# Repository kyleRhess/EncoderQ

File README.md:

# EncoderQ

## A realtime embedded C program for interfacing with incremental rotary encoders

 This code has been written for and tested on an ARM STM32F4 processor with a timer peripheral that supports for quadrature encoder input.
\
\
Currently, the processor hardware from the [DroneFluxx](https://github.com/kyleRhess/DroneFluxx) project is being used for testing firmware.
\
The only rotary encoder that has been tested so far is the [E6D-C](http://www.ia.omron.com/data_pdf/cat/e6d-c_ds_e_5_1_csm497.pdf) from Omron. This is a 6,000 pulse/revolution incremental encoder. This encoder is capable of quadrature operation which essentially means it can output up to (4*6,000) = 24,000 pulses/revolution.

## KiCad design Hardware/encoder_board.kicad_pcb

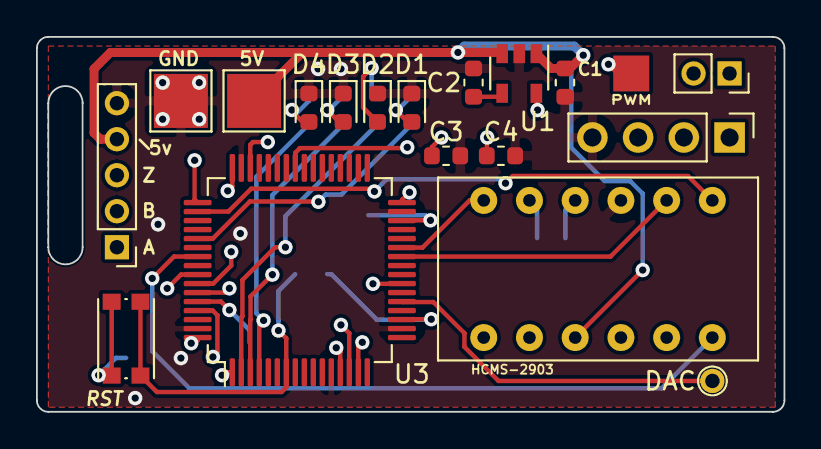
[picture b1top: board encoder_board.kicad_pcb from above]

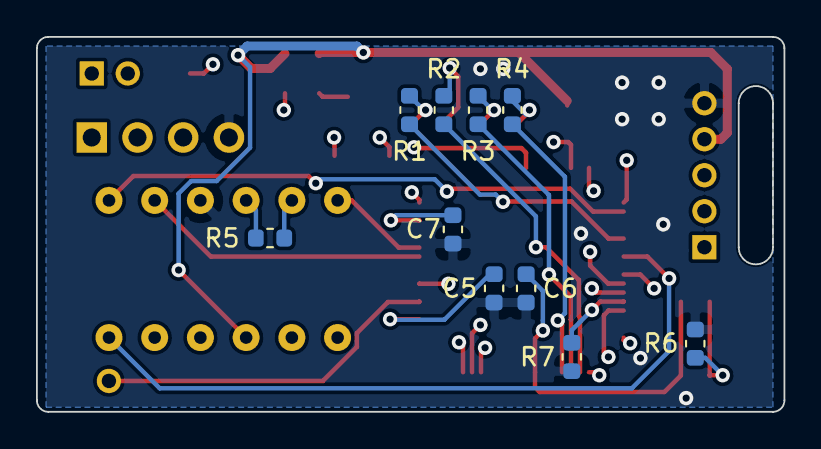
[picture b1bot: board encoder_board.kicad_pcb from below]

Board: 4 copper layers, 41.5 x 20.8 mm, 29 parts (10 on the bottom side), 32 nets.

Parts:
C1: 1uF; C_0603_1608Metric
C2, C5: 10nF; C_0603_1608Metric
C3, C7: 2.2uF; C_0603_1608Metric
C4, C6: 0.1uF; C_0603_1608Metric
D1, D2, D3, D4: LED; LED_0603_1608Metric
DAC: Conn_01x01_Female; TestPoint_Plated_Hole_D2.0mm
HCMS-2903: HCMS-2903; HCMS-290x
J1: Conn_01x02_Female; PinSocket_1x02_P2.00mm_Vertical
J2: Conn_01x04_Male; PinHeader_1x04_P2.54mm_Vertical
J3: Conn_01x05_Male; PinHeader_1x05_P2.00mm_Vertical
J5, J6: Conn_01x01_Female; TestPoint_Pad_3.0x3.0mm
PWM: Conn_01x01_Female; TestPoint_Pad_3.0x3.0mm
R1, R2, R3, R4, R6: 470; R_0603_1608Metric
R5, R7: 10k; R_0603_1608Metric
RST: SW_Push; SW_Push_1P1T_NO_CK_KMR2
U1: LP2985-3.3; SOT-23-5
U3: STM32F410RBTx; LQFP-64_10x10mm_P0.5mm

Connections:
+3V3: C3.1, C4.1, C5.1, HCMS-2903.11, J2.3, R5.1, U1.5, U3.1, U3.13, U3.19, U3.32, U3.48, U3.64
+5V: C1.1, HCMS-2903.3, J3.4, J6.1, U1.1, U1.3
BLANK: HCMS-2903.8, U3.26
DAC_1: DAC.1, U3.21
GND: C1.2, C2.2, C3.2, C4.2, C5.2, C6.2, C7.2, D1.1, D2.1, D3.1, D4.1, HCMS-2903.9, J2.4, J3.5, J5.1, R6.1, R7.1, U1.2, U3.12, U3.18, U3.31, U3.47, U3.63
LED_A: R1.1, U3.53
LED_B: R2.1, U3.2
LED_C: R3.1, U3.3
LED_D: R4.1, U3.4
LRESET: HCMS-2903.12, U3.27
unnamed: C2.1, U1.4
unnamed: C6.1, RST.2, U3.7
unnamed: C7.1, U3.30
unnamed: D1.2, R1.2
unnamed: D2.2, R2.2
unnamed: D3.2, R3.2
unnamed: D4.2, R4.2
unnamed: HCMS-2903.10, R5.2
unnamed: R6.2, RST.1
unnamed: R7.2, U3.60
OUTA: J3.1, U3.14
OUTB: J3.2, U3.15
OUTZ: J3.3, U3.23
PWM1: PWM.1, U3.41
RS: HCMS-2903.5, U3.61
SPI1_CLK: HCMS-2903.6, U3.55
SPI1_CS0: HCMS-2903.7, U3.50
SPI1_MOSI: HCMS-2903.4, U3.57
SWCLK: J2.2, U3.49
SWDIO: J2.1, U3.46
USART1_RX: J1.2, U3.59
USART1_TX: J1.1, U3.58

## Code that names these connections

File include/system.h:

#ifndef SYSTEM_H_ /* include guard */
#define SYSTEM_H_

#define LED_A 				GPIO_PIN_12
#define LED_B 				GPIO_PIN_13
#define LED_C 				GPIO_PIN_14
#define LED_D 				GPIO_PIN_15
#define LED_PORT 			GPIOC

#define UART_PORT			GPIOB
#define UART_TX_PIN			GPIO_PIN_6
#define UART_RX_PIN			GPIO_PIN_7

#define ADC_PORT			GPIOA
#define ADC_THROTTLE		GPIO_PIN_5

#define POWER_SW_PORT		GPIOA
#define POWER_SW_PIN		GPIO_PIN_7

#include "stm32f4xx_hal.h"
#include "signal.h"

void WritePin(GPIO_TypeDef* GPIOx, uint16_t GPIO_Pin, GPIO_PinState PinState);
uint8_t ReadPin(GPIO_TypeDef* GPIOx, uint16_t GPIO_Pin);

float mapVal(float x, float in_min, float in_max, float out_min, float out_max);


#endif /* SYSTEM_H_ */

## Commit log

2020-07-25 Updated project for new install of Eclipse
2020-07-26 Added files for Travis CI
2020-07-26 Fixed .yml file
2020-07-26 More yml file fixes...
2020-07-26 Stopped trying CI. Removed .yml file.
2020-08-06 Fixed some project settings
2020-08-08 Created custom board for embedded display.
2020-08-09 Board ordered.
2020-08-10 Added support for a PWM output.
2020-08-31 Added initial support for 4 character display.
2020-09-01 Changed to adding n chars vs just one.
2020-09-02 Added UART support for displaying characters rx'd over serial.
2021-01-16 Implemented DMA for UART interface. Fixed PWM signal generation.
2021-02-03 Made initial changes for 3 channel complementary PWM generation.
2021-02-10 Primitive SVM is now working okay.
2021-02-11 Cleaned out unused code in main
2021-05-10 Began changes to use hardware as ebike serial HID.
2021-07-27 Test commit
